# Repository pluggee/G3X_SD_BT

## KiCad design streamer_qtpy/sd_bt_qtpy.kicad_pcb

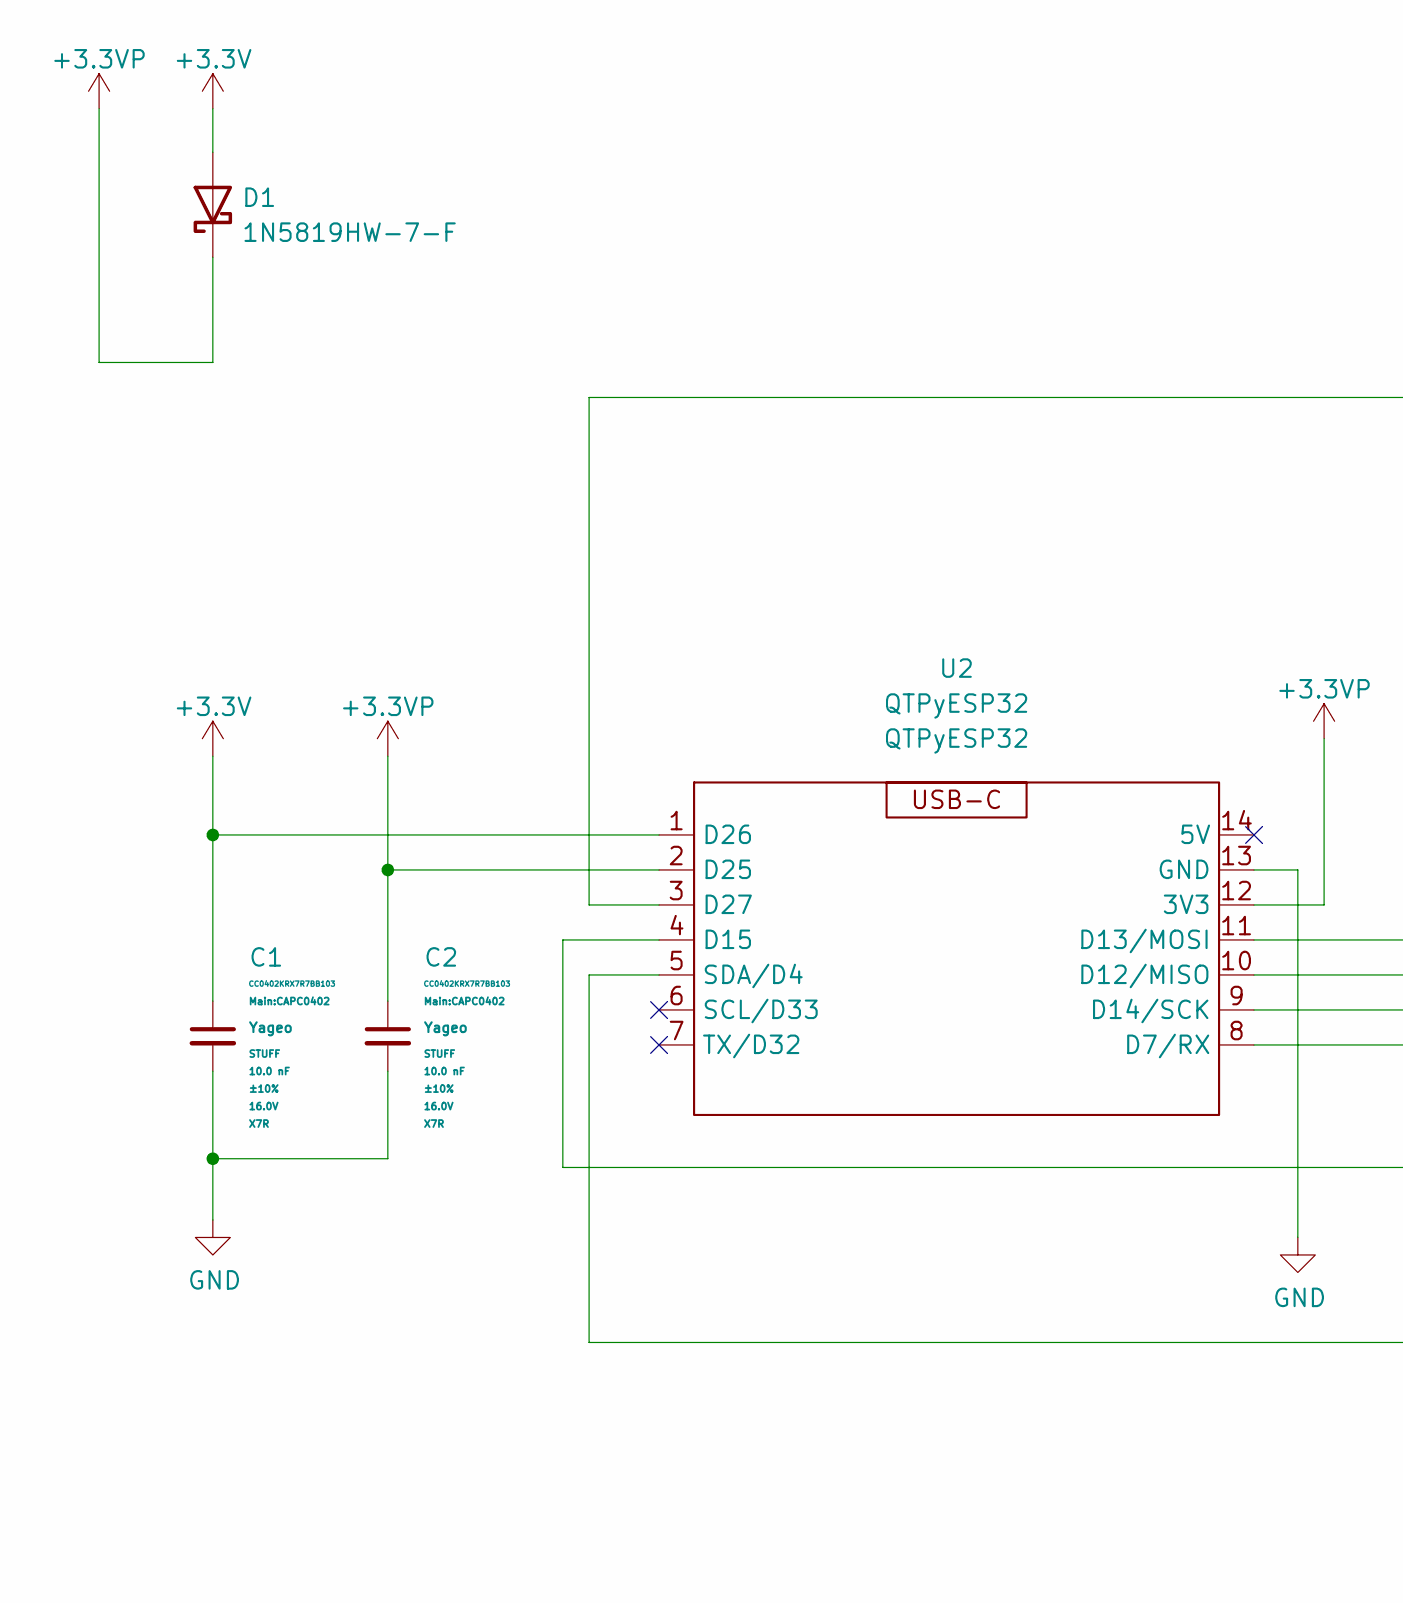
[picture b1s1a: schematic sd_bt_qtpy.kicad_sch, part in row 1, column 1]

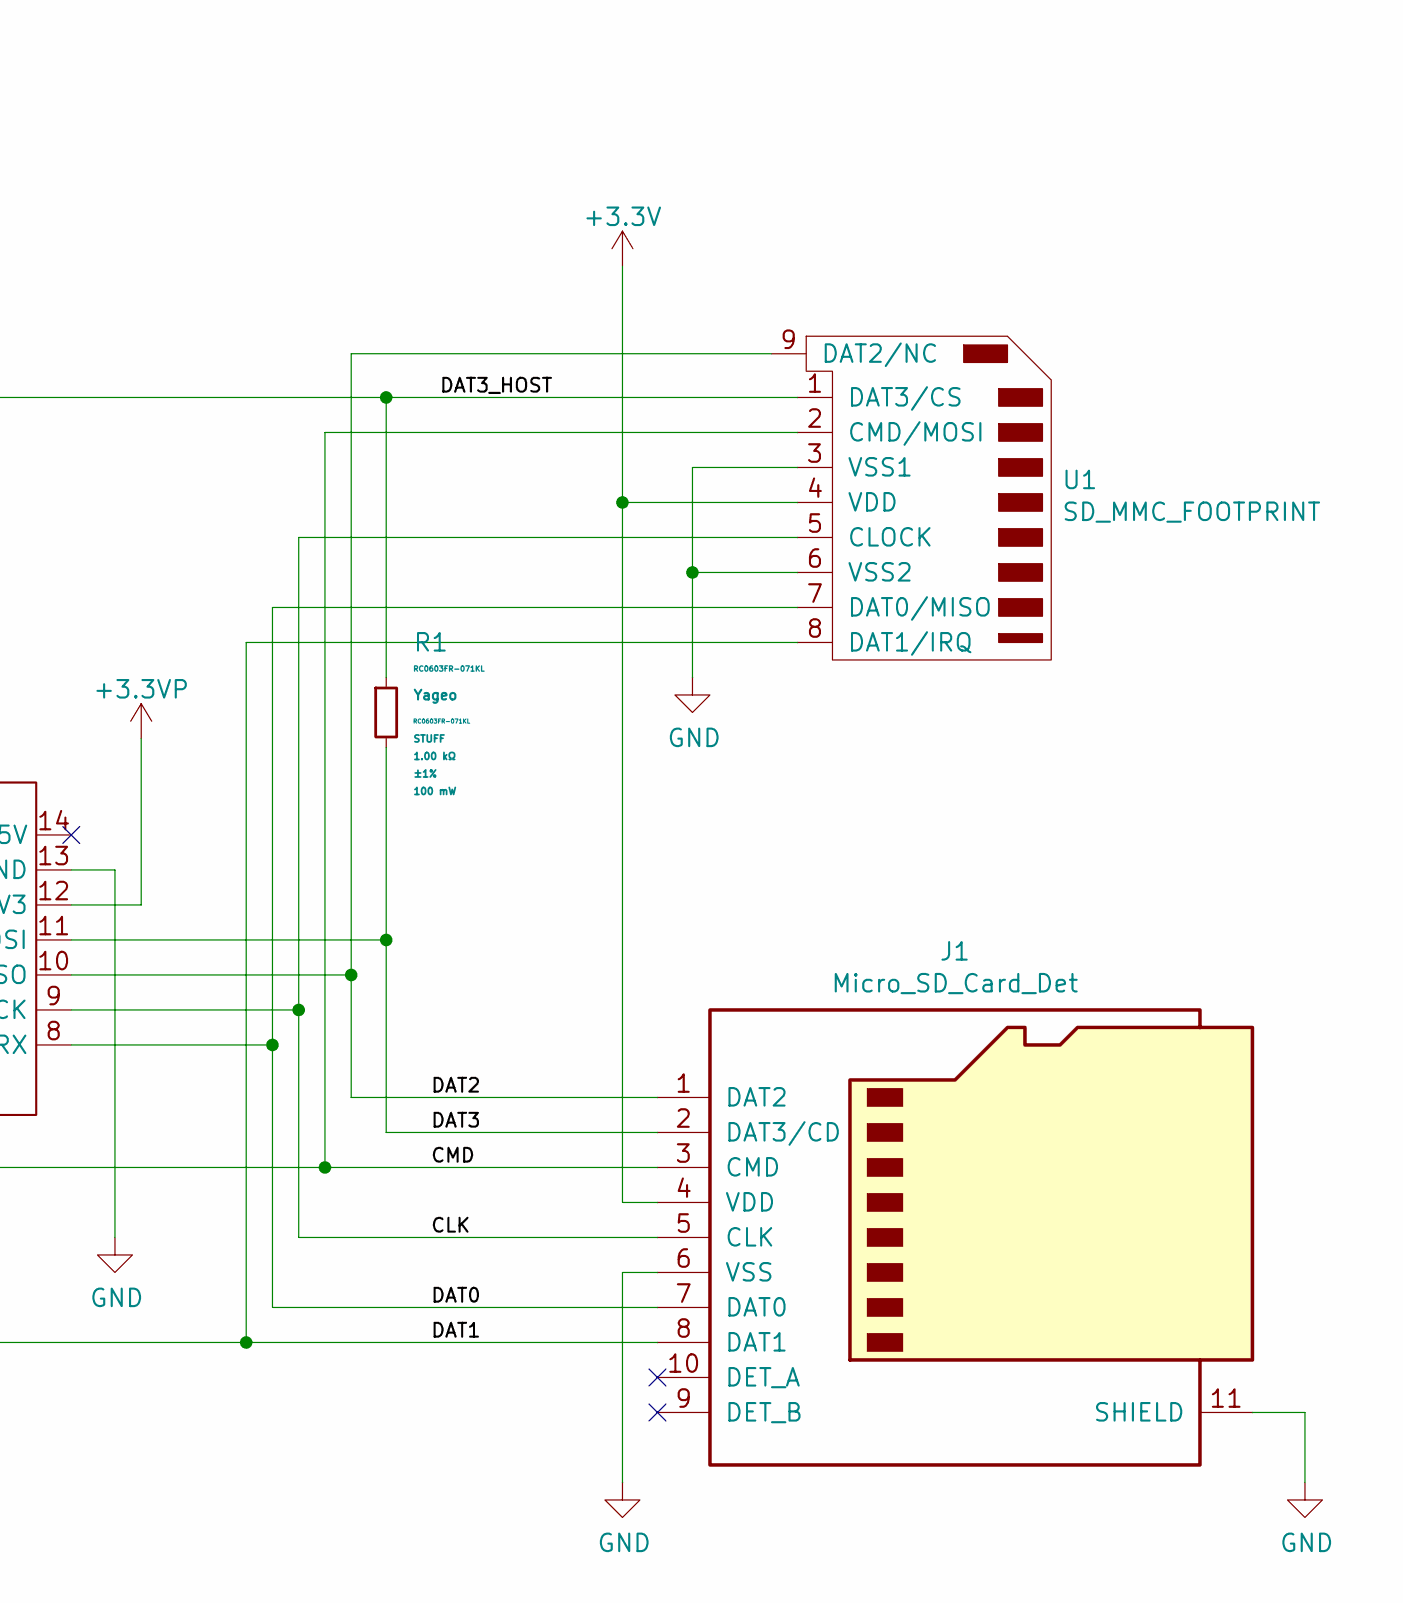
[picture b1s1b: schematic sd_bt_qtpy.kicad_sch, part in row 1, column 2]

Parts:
C1, C2: CC0402KRX7R7BB103; CAPC0402; MPN CC0402KRX7R7BB103
D1: 1N5819HW-7-F; D_SOD-123; MPN C82544
J1: Micro_SD_Card_Det; microSD_HC_Molex_104031-0811; MPN C585350
R1: RC0603FR-071KL; RESC0603; MPN RC0603FR-071KL
U1: SD_MMC_FOOTPRINT; SD_MMC_CARD
U2: QTPyESP32; MPN QTPyESP32

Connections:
+3.3V: C1.1, D1.2 (A), J1.4 (VDD), U1.4 (VDD), U2.1 (D26)
+3.3VP: C2.1, D1.1 (K), U2.2 (D25), U2.12 (3V3)
/CLK: J1.5 (CLK), U1.5 (CLOCK), U2.9 (D14/SCK)
/CMD: J1.3 (CMD), U1.2 (CMD/MOSI), U2.4 (D15)
/DAT0: J1.7 (DAT0), U1.7 (DAT0/MISO), U2.8 (D7/RX)
/DAT1: J1.8 (DAT1), U1.8 (DAT1/IRQ), U2.5 (SDA/D4)
/DAT2: J1.1 (DAT2), U1.9 (DAT2/NC), U2.10 (D12/MISO)
/DAT3: J1.2 (DAT3/CD), R1.2, U2.11 (D13/MOSI)
/DAT3_HOST: R1.1, U1.1 (DAT3/CS), U2.3 (D27)
GND: C1.2, C2.2, J1.6 (VSS), J1.11 (SHIELD), U1.3 (VSS1), U1.6 (VSS2), U2.13 (GND)

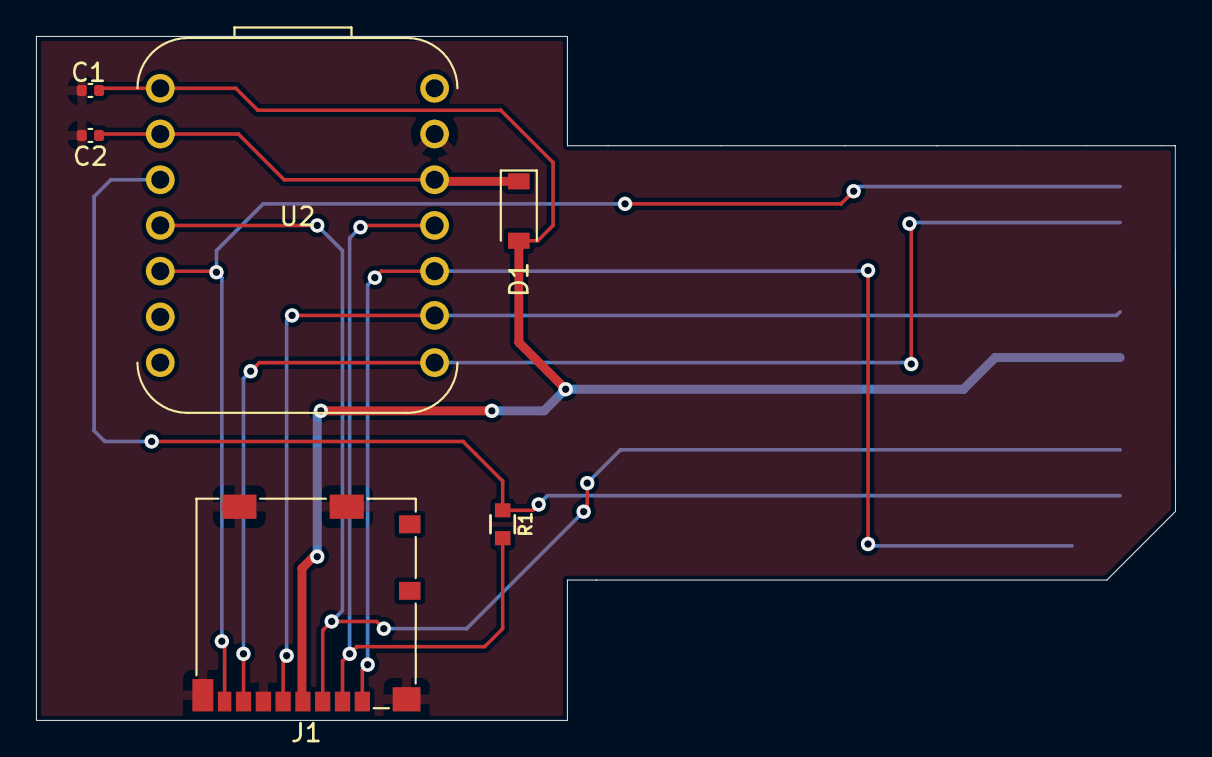
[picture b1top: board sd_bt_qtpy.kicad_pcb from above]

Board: 2 copper layers, 63.3 x 38.0 mm, 7 parts (1 on the bottom side), 10 nets.

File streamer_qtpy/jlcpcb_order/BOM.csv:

Reference(s),Value,Footprint,MPN
"C1, C2",CC0402KRX7R7BB103,Main:CAPC0402,CC0402KRX7R7BB103
D1,1N5819HW-7-F,Diode_SMD:D_SOD-123,C82544
J1,Micro_SD_Card_Det,Connector_Card:microSD_HC_Molex_104031-0811,C585350
R1,RC0603FR-071KL,Main:RESC0603,RC0603FR-071KL

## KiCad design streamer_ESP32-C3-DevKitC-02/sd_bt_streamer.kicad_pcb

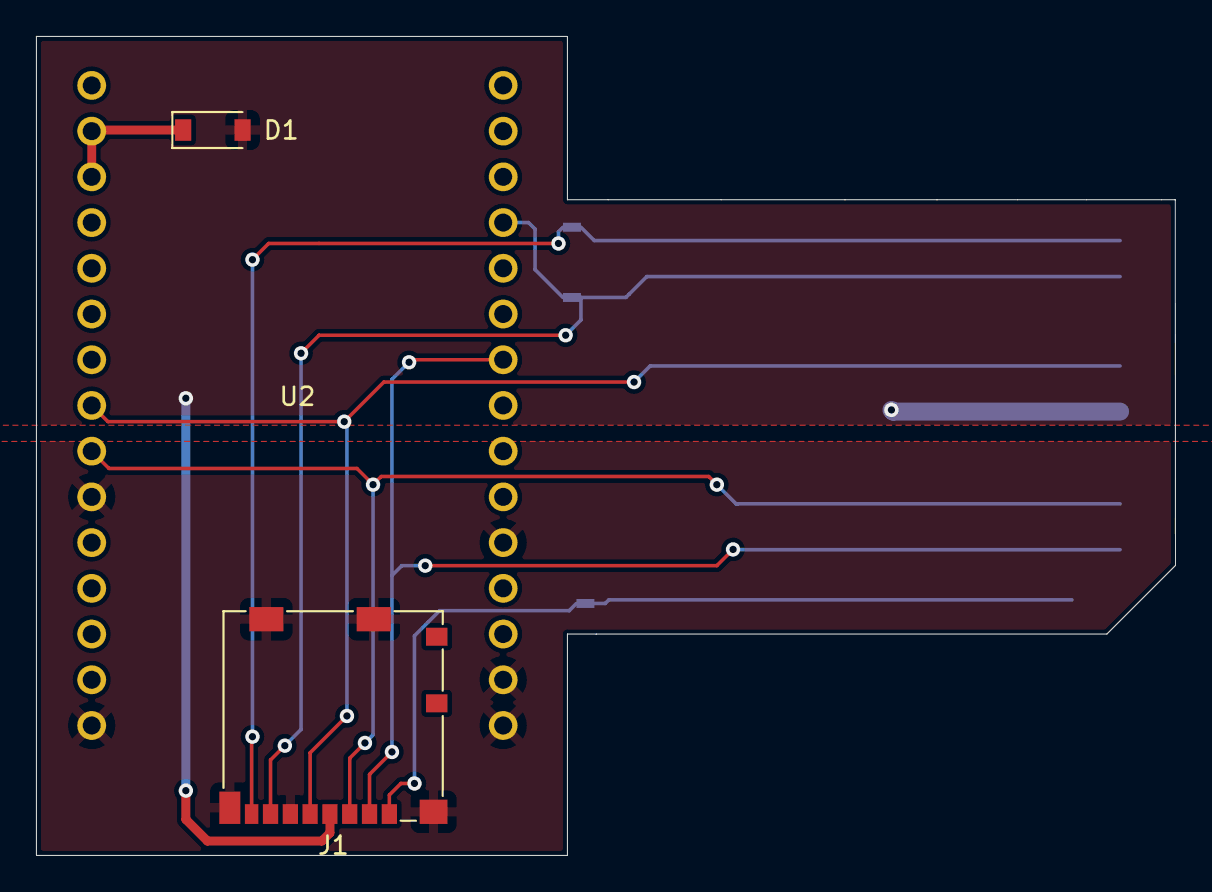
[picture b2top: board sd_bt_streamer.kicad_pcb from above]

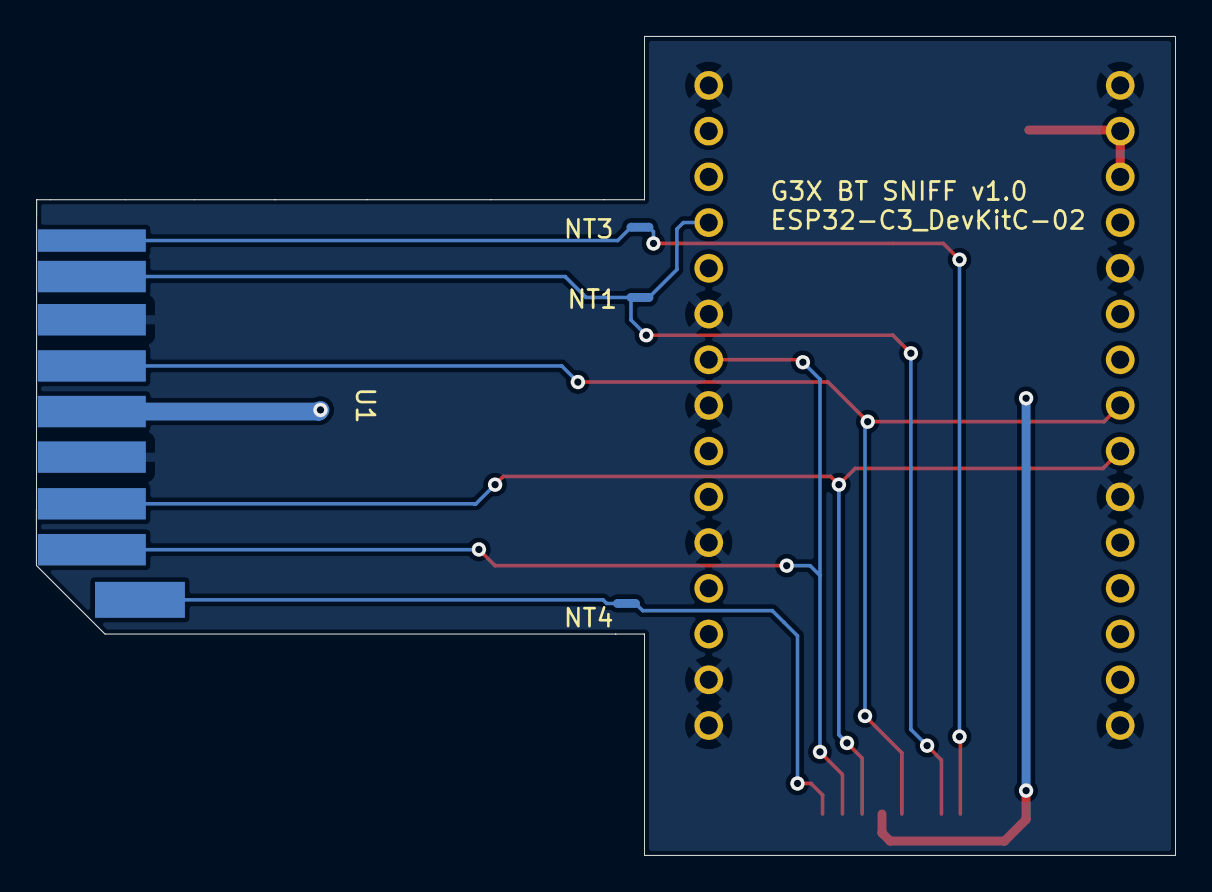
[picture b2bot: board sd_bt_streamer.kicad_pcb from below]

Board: 2 copper layers, 63.3 x 45.5 mm, 7 parts (4 on the bottom side), 12 nets.

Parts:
D1: 1N5819HW-7-F; D_SOD-123
J1: Micro_SD_Card_Det; microSD_HC_Molex_104031-0811
NT1, NT3, NT4: NetTie_2; NetTie-2_SMD_Pad0.5mm
U1: SD_MMC_FOOTPRINT; SD_MMC_CARD
U2: ESP32-C3-DevKitC-02

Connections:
+3.3V: D1.2 (A), J1.4 (VDD), U1.4 (VDD)
+3.3VP: D1.1 (K), U2.2 (3V3), U2.3 (3V3)
/CLK: J1.5 (CLK), U1.5 (CLOCK), U2.8 (GPIO6/SCK)
/CS: J1.2 (DAT3/CD), U1.1 (DAT3/CS), U2.24 (GPIO10/CS0)
/DAT1: J1.8 (DAT1), NT3.1
/DAT1_T: NT3.2, U1.8 (DAT1/IRQ)
/DAT2: J1.1 (DAT2), NT4.1
/DAT2_T: NT4.2, U1.9 (DAT2/NC)
/MISO: J1.7 (DAT0), NT1.2, U1.7 (DAT0/MISO)
/MISO_ESP32: NT1.1, U2.27 (GPIO2/MISO)
/MOSI: J1.3 (CMD), U1.2 (CMD/MOSI), U2.9 (GPIO7/MOSI)
GND: J1.6 (VSS), J1.11 (SHIELD), U1.3 (VSS1), U1.6 (VSS2), U2.1 (GND), U2.5 (GND), U2.10 (GND), U2.15 (GND), U2.16 (GND), U2.17 (GND), U2.20 (GND), U2.23 (GND), U2.25 (GND), U2.30 (GND)

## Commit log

2022-02-25 added gerber zip
2022-06-01 extended SD card by 5mm
2022-08-04 gerbered out ESP32-DevKitC
2022-08-04 moved ESP32-DevKitC to separate directory
2022-08-04 added ESP32-C3-DevKit-02 board
2022-09-20 added qtpy sd mmc version
2022-09-20 ordered from jlcpcb
